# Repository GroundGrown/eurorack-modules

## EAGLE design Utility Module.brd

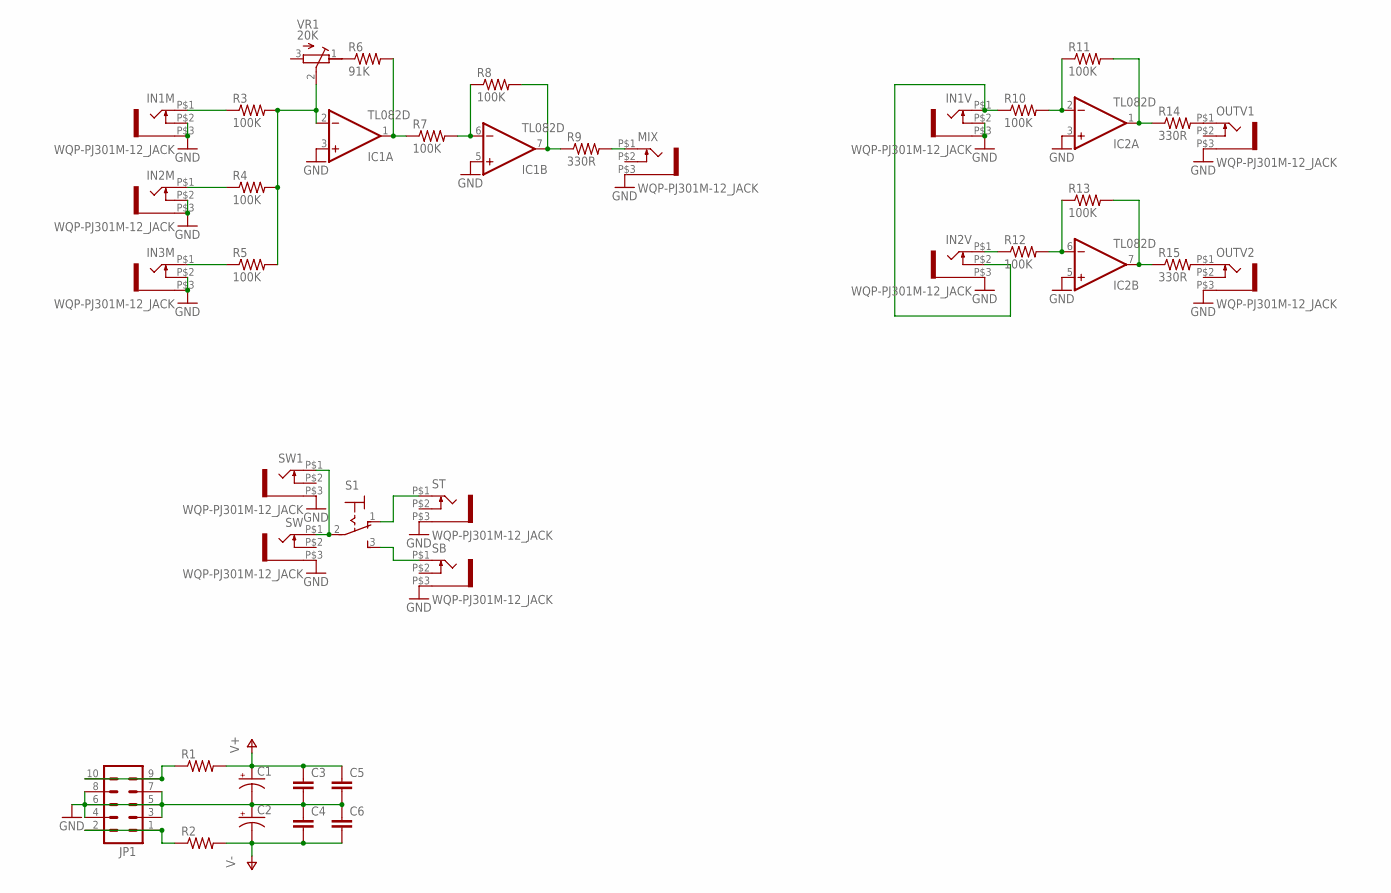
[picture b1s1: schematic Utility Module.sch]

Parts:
C1, C2: CAP_POLC; PANASONIC_C
C3, C4, C5, C6: CAP0805; 0805
IC1, IC2: TL082D; SO08
IN1M, IN1V, IN2M, IN2V, IN3M: WQP-PJ301M-12_JACK
JP1: M05X2PTH; AVR_ICSP
MIX: WQP-PJ301M-12_JACK
OUTV1, OUTV2: WQP-PJ301M-12_JACK
R1, R2: RESISTOR0805-RES; 0805
R3, R4, R5, R7, R8, R10, R11, R12, R13: 100K; 0805
R6: 91K; 0805
R9, R14, R15: 330R; 0805
S1: M9040P
SB: WQP-PJ301M-12_JACK
ST: WQP-PJ301M-12_JACK
SW, SW1: WQP-PJ301M-12_JACK
VR1: 20K; RTRIM3314G

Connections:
GND: C1.-, C2.+, C3.2, C4.1, C5.2, C6.1, IC1.3 (+IN), IC1.5 (+IN), IC2.3 (+IN), IC2.5 (+IN), IN1M.P$2 (3), IN1M.P$3 (1), IN1V.P$2 (3), IN1V.P$3 (1), IN2M.P$2 (3), IN2M.P$3 (1), IN2V.P$3 (1), IN3M.P$2 (3), IN3M.P$3 (1), JP1.3, JP1.4, JP1.5, JP1.6, JP1.7, JP1.8, MIX.P$3 (1), OUTV1.P$3 (1), OUTV2.P$3 (1), SB.P$3 (1), ST.P$3 (1), SW.P$3 (1), SW1.P$3 (1)
unnamed: R6.1, VR1.1 (E)
unnamed: IN1M.P$1 (2), R3.1
unnamed: JP1.9, JP1.10, R1.1
unnamed: JP1.1, JP1.2, R2.1
unnamed: IN2M.P$1 (2), R4.1
unnamed: IN3M.P$1 (2), R5.1
unnamed: IC1.2 (-IN), R3.2, R4.2, R5.2, VR1.2 (S)
unnamed: MIX.P$1 (2), R9.2
unnamed: IC1.1 (OUT), R6.2, R7.1
unnamed: IC1.6 (-IN), R7.2, R8.1
unnamed: IC1.7 (OUT), R8.2, R9.1
unnamed: IN1V.P$1 (2), IN2V.P$2 (3), R10.1
unnamed: S1.2, SW.P$1 (2), SW1.P$1 (2)
unnamed: IN2V.P$1 (2), R12.1
unnamed: IC2.6 (-IN), R12.2, R13.1
unnamed: IC2.2 (-IN), R10.2, R11.1
unnamed: IC2.1 (OUT), R11.2, R14.1
unnamed: IC2.7 (OUT), R13.2, R15.1
unnamed: OUTV1.P$1 (2), R14.2
unnamed: OUTV2.P$1 (2), R15.2
unnamed: S1.1 (O), ST.P$1 (2)
unnamed: S1.3 (S), SB.P$1 (2)
V+: C1.+, C3.1, C5.1, IC1.8 (V+), IC2.8 (V+), R1.2
V-: C2.-, C4.2, C6.2, IC1.4 (V-), IC2.4 (V-), R2.2

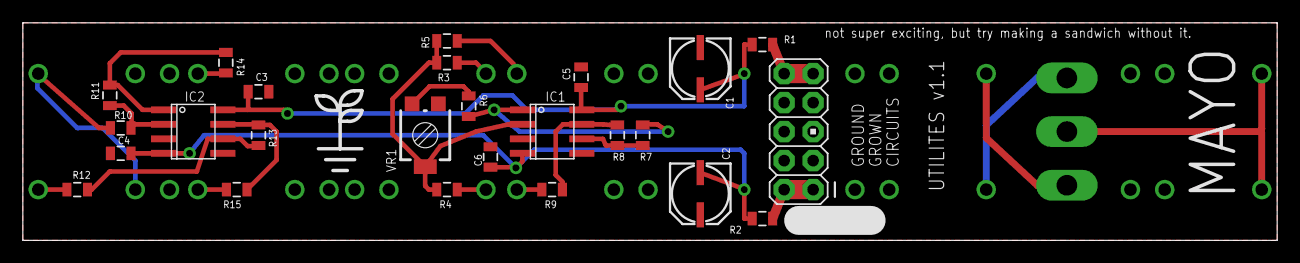
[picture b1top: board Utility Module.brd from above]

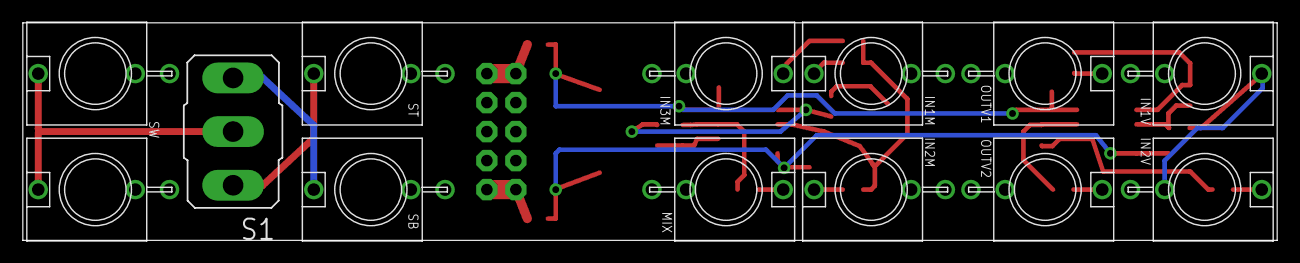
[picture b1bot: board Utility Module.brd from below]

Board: 2 copper layers, 109.9 x 19.1 mm, 39 parts (13 on the bottom side), 25 nets.

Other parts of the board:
U$1: LOGO_SMALL

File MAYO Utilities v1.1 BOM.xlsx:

2 | FERRITE BEAD | R1, R2
3 | 330 ohm | R9, R14, R15
1 | 91K | R6
9 | 100K | R3, R4, R5, R7, R8, R10, R11, R12, R13
4 | .1u | C3, C4, C5, C6
2 | 10u | C1, C2
1 | 20K Trim | VR1
2 | TL082 | IC1, IC2
1 | 2x5 pos male .1" Header | JP1
12 | WQP-PJ301M-12_JACK | IN1M, IN2M, IN3M, MIX, IN1V, IN2V, OUTV1, OUTV2, SW, SW1, ST, SB
1 | ON-OFF-ON toggle M9040P | S1

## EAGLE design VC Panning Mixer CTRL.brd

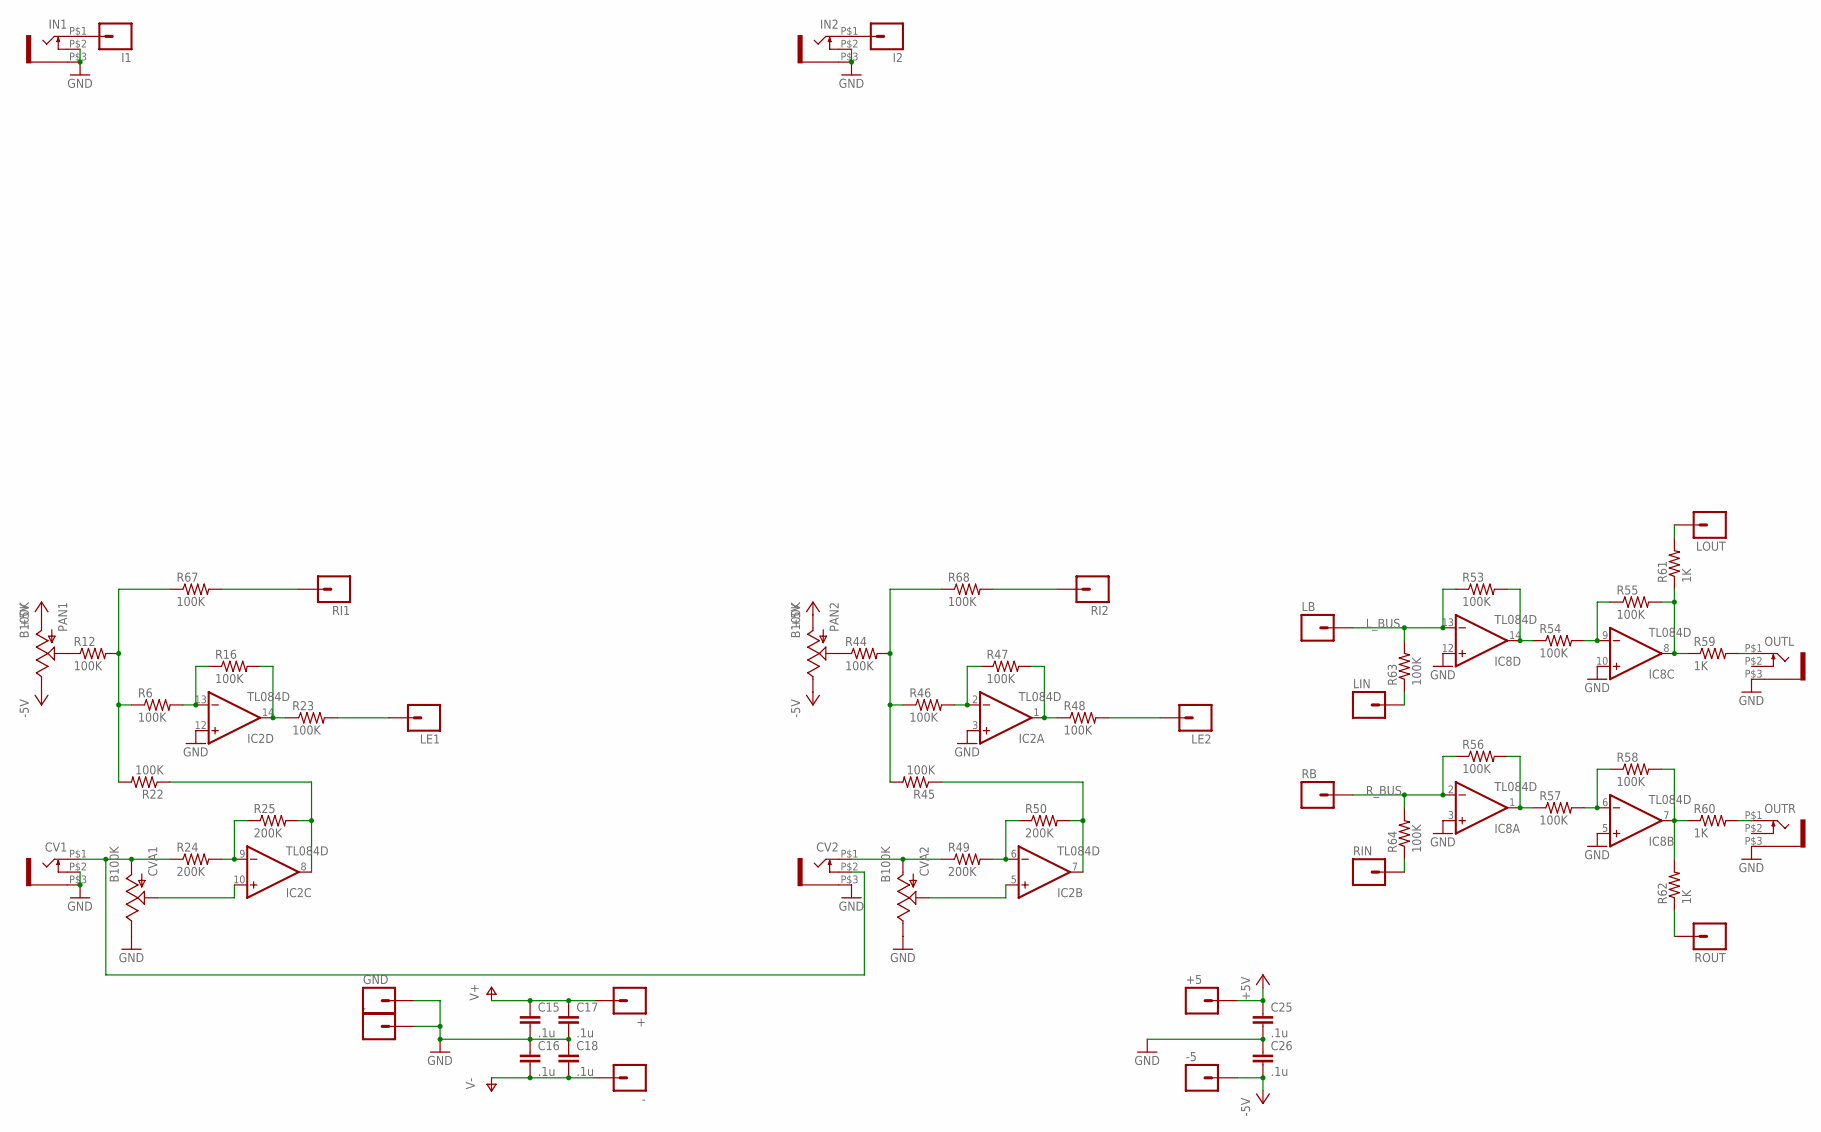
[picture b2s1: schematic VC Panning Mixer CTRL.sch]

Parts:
+, +5: M01PTH; 1X01
-, -5: M01PTH; 1X01
.: M01PTH; 1X01
C15, C16, C17, C18, C25, C26: .1u; 0805
CV1, CV2: WQP-PJ301M-12_JACK
CVA1, CVA2: B100K; ALPS_POT
GND: M01PTH; 1X01
I1, I2: M01PTH; 1X01
IC2, IC8: TL084D; SO14
IN1, IN2: WQP-PJ301M-12_JACK
LB: M01PTH; 1X01
LE1, LE2: M01PTH; 1X01
LIN: M01PTH; 1X01
LOUT: M01PTH; 1X01
OUTL: WQP-PJ301M-12_JACK
OUTR: WQP-PJ301M-12_JACK
PAN1, PAN2: B100K; ALPS_POT
R6, R12, R16, R22, R23, R44, R45, R46, R47, R48, R53, R54, R55, R56, R57, R58, R63, R64, R67, R68: 100K; 0805
R24, R25, R49, R50: 200K; 0805
R59, R60, R61, R62: 1K; 0805
RB: M01PTH; 1X01
RI1, RI2: M01PTH; 1X01
RIN: M01PTH; 1X01
ROUT: M01PTH; 1X01

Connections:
+5V: +5.1, C25.1, PAN1.P$3 (A), PAN2.P$3 (A)
-5V: -5.1, C26.2, PAN1.P$1 (E), PAN2.P$1 (E)
GND: ..1, C15.2, C16.1, C17.2, C18.1, C25.2, C26.1, CV1.P$2 (3), CV1.P$3 (1), CV2.P$3 (1), CVA1.P$1 (E), CVA2.P$1 (E), GND.1, IC2.3 (+IN), IC2.12 (+IN), IC8.3 (+IN), IC8.5 (+IN), IC8.10 (+IN), IC8.12 (+IN), IN1.P$2 (3), IN1.P$3 (1), IN2.P$2 (3), IN2.P$3 (1), OUTL.P$3 (1), OUTR.P$3 (1)
L_BUS: IC8.13 (-IN), LB.1, R53.1, R63.2
unnamed: R68.2, RI2.1
unnamed: R67.2, RI1.1
unnamed: I1.1, IN1.P$1 (2)
unnamed: I2.1, IN2.P$1 (2)
unnamed: R6.1, R12.2, R22.2, R67.1
unnamed: LE1.1, R23.2
unnamed: LE2.1, R48.2
unnamed: R44.2, R45.2, R46.1, R68.1
unnamed: PAN1.P$2 (S), R12.1
unnamed: CV1.P$1 (2), CV2.P$2 (3), CVA1.P$3 (A), R24.1
unnamed: CVA1.P$2 (S), IC2.10 (+IN)
unnamed: IC2.9 (-IN), R24.2, R25.1
unnamed: IC2.8 (OUT), R22.1, R25.2
unnamed: IC2.13 (-IN), R6.2, R16.1
unnamed: IC2.14 (OUT), R16.2, R23.1
unnamed: PAN2.P$2 (S), R44.1
unnamed: CV2.P$1 (2), CVA2.P$3 (A), R49.1
unnamed: CVA2.P$2 (S), IC2.5 (+IN)
unnamed: IC2.6 (-IN), R49.2, R50.1
unnamed: IC2.7 (OUT), R45.1, R50.2
unnamed: IC2.2 (-IN), R46.2, R47.1
unnamed: IC2.1 (OUT), R47.2, R48.1
unnamed: IC8.14 (OUT), R53.2, R54.1
unnamed: IC8.9 (-IN), R54.2, R55.1
unnamed: IC8.8 (OUT), R55.2, R59.1, R61.1
unnamed: IC8.1 (OUT), R56.2, R57.1
unnamed: IC8.6 (-IN), R57.2, R58.1
unnamed: IC8.7 (OUT), R58.2, R60.1, R62.2
unnamed: OUTL.P$1 (2), R59.2
unnamed: OUTR.P$1 (2), R60.2
unnamed: R64.1, RIN.1
unnamed: LIN.1, R63.1
unnamed: LOUT.1, R61.2
unnamed: R62.1, ROUT.1
R_BUS: IC8.2 (-IN), R56.1, R64.2, RB.1
V+: +.1, C15.1, C17.1, IC2.4 (V+), IC8.4 (V+)
V-: -.1, C16.2, C18.2, IC2.11 (V-), IC8.11 (V-)

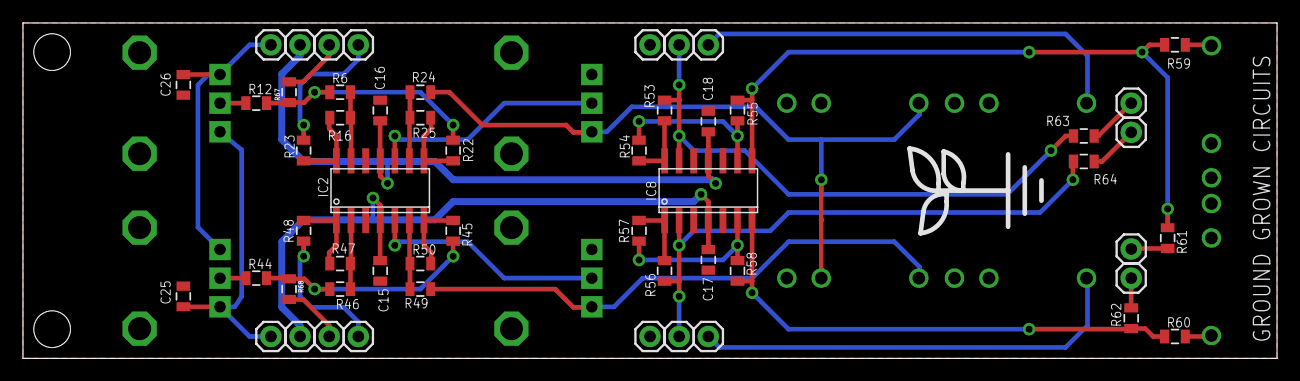
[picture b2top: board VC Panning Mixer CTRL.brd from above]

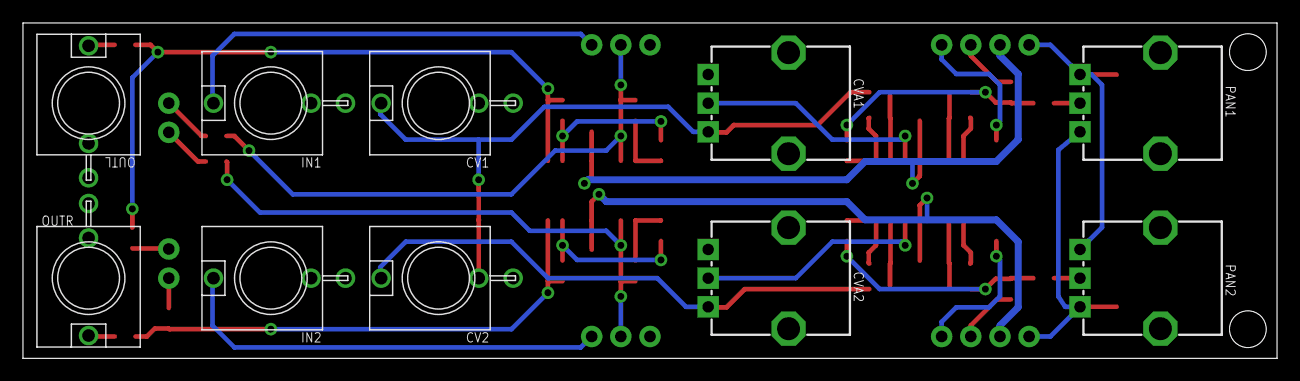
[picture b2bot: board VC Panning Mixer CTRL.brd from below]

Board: 2 copper layers, 109.2 x 29.2 mm, 65 parts (10 on the bottom side), 41 nets.

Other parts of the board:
U$1: LOGO_MED

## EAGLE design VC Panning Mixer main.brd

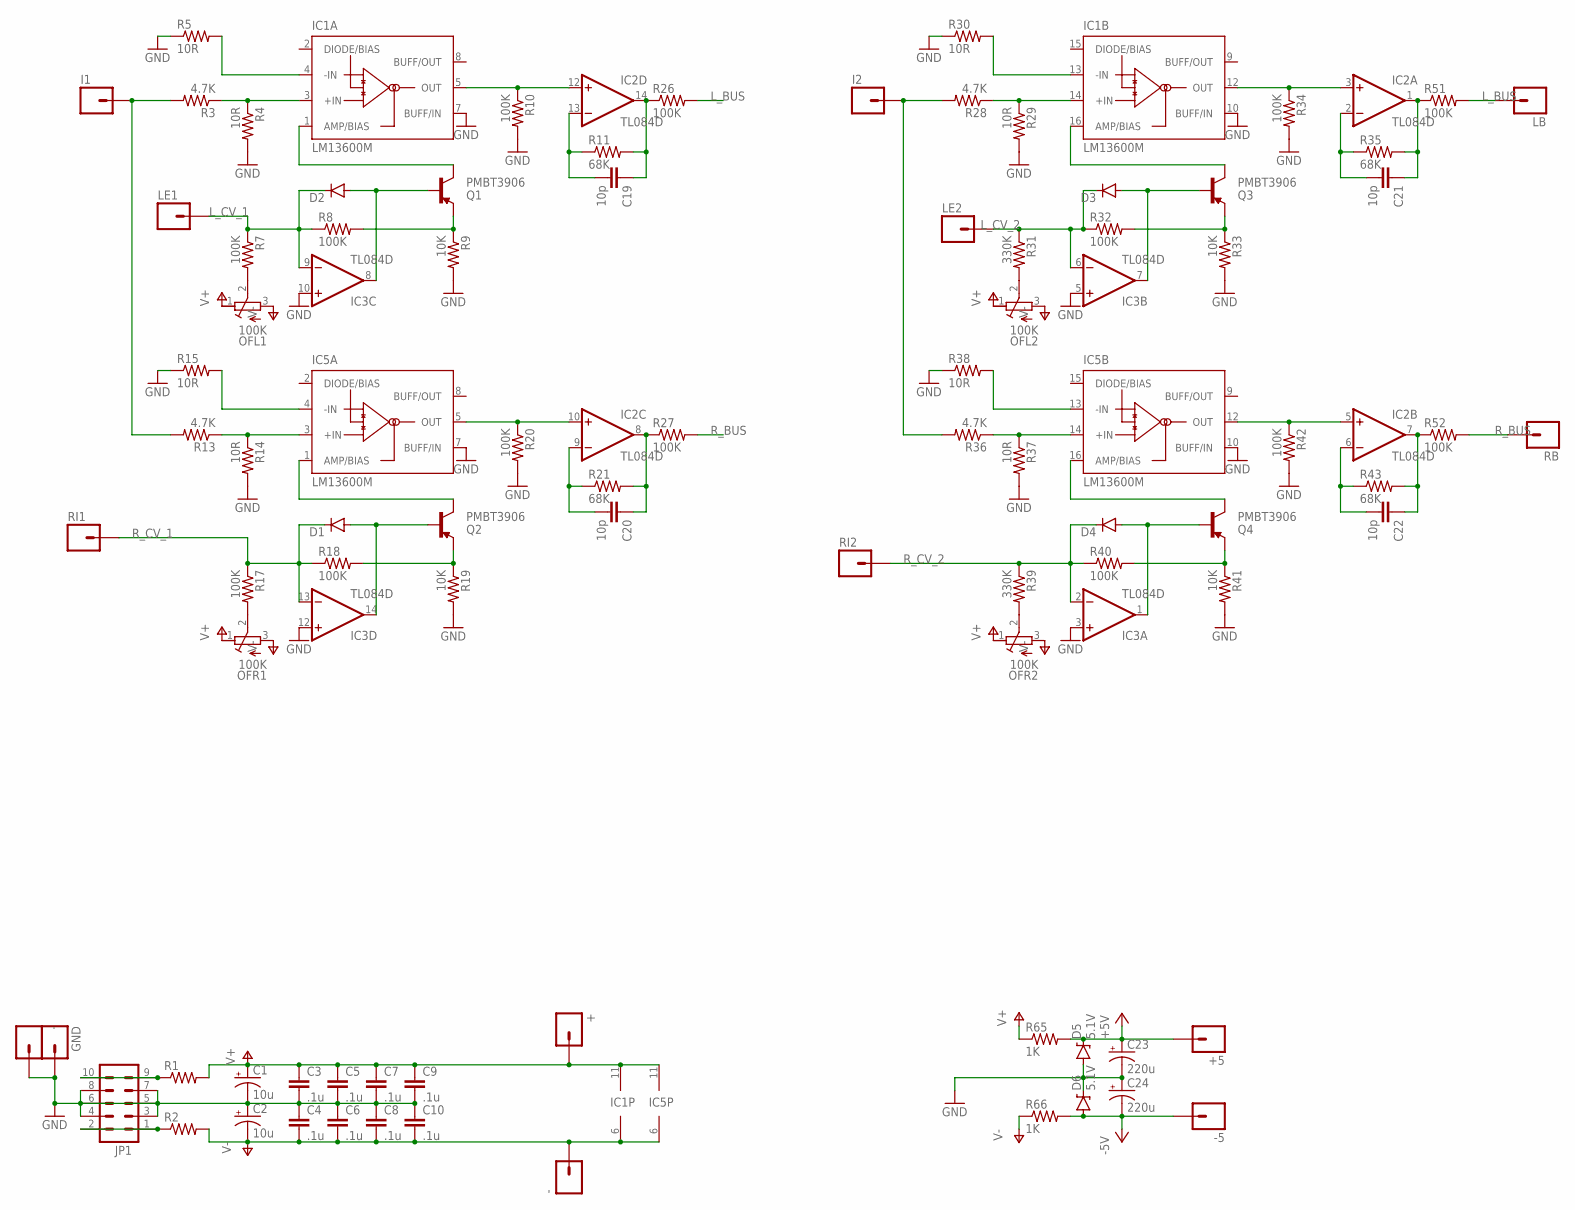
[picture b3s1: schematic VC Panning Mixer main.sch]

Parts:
+, +5: M01PTH; 1X01
-, -5: M01PTH; 1X01
.: M01PTH; 1X01
C1, C2: 10u; CPOL-RADIAL-10UF-25V
C3, C4, C5, C6, C7, C8, C9, C10: .1u; 0805
C19, C20, C21, C22: 10p; 0805
C23, C24: 220u; CPOL-RADIAL-10UF-25V
D1, D2, D3, D4: DIODESOD123; SOD-123
D5, D6: 5.1V; SOD-123
GND: M01PTH; 1X01
I1, I2: M01PTH; 1X01
IC1, IC5: LM13600M; SO16
IC2, IC3: TL084D; SO14
JP1: M05X2PTH; AVR_ICSP
LB: M01PTH; 1X01
LE1, LE2: M01PTH; 1X01
OFL1, OFL2: 100K; RTRIM3314G
OFR1, OFR2: 100K; RTRIM3314G
Q1, Q2, Q3, Q4: PMBT3906; SOT23-3
R1, R2: RESISTOR0805-RES; 0805@1
R3, R13, R28, R36: 4.7K; 0805
R4, R5, R14, R15, R29, R30, R37, R38: 10R; 0805
R7, R8, R10, R17, R18, R20, R26, R27, R32, R34, R40, R42, R51, R52: 100K; 0805
R9, R19, R33, R41: 10K; 0805
R11, R21, R35, R43: 68K; 0805
R31, R39: 330K; 0805
R65, R66: 1K; 0805
RB: M01PTH; 1X01
RI1, RI2: M01PTH; 1X01

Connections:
+5V: +5.1, C23.1 (+), D5.C, R65.2
-5V: -5.1, C24.2 (-), D6.A, R66.2
GND: ..1, C1.2 (-), C2.1 (+), C3.2, C4.1, C5.2, C6.1, C7.2, C8.1, C9.2, C10.1, C23.2 (-), C24.1 (+), D5.A, D6.C, GND.1, IC1.7 (BUFF/IN), IC1.10 (BUFF/IN), IC3.3 (+IN), IC3.5 (+IN), IC3.10 (+IN), IC3.12 (+IN), IC5.7 (BUFF/IN), IC5.10 (BUFF/IN), JP1.3, JP1.4, JP1.5, JP1.6, JP1.7, JP1.8, R4.2, R5.1, R9.2, R10.2, R14.2, R15.1, R19.2, R20.2, R29.2, R30.1, R33.2, R34.2, R37.2, R38.1, R41.2, R42.2
L_BUS: LB.1, R26.2, R51.2
L_CV_1: D2.C, IC3.9 (-IN), LE1.1, R7.1, R8.1
L_CV_2: D3.C, IC3.6 (-IN), LE2.1, R31.1, R32.1
unnamed: JP1.9, JP1.10, R1.1
unnamed: JP1.1, JP1.2, R2.1
unnamed: I1.1, R3.2, R13.2
unnamed: IC5.3 (+IN), R13.1, R14.1
unnamed: IC5.4 (-IN), R15.2
unnamed: OFR1.2 (S), R17.2
unnamed: Q2.2 (E), R18.2, R19.1
unnamed: D1.A, IC3.14 (OUT), Q2.1 (B)
unnamed: IC5.1 (AMP/BIAS), Q2.3 (C)
unnamed: IC1.3 (+IN), R3.1, R4.1
unnamed: IC2.10 (+IN), IC5.5 (OUT), R20.1
unnamed: IC1.4 (-IN), R5.2
unnamed: OFL1.2 (S), R7.2
unnamed: Q1.2 (E), R8.2, R9.1
unnamed: D2.A, IC3.8 (OUT), Q1.1 (B)
unnamed: C20.2, IC2.9 (-IN), R21.1
unnamed: IC1.1 (AMP/BIAS), Q1.3 (C)
unnamed: IC1.5 (OUT), IC2.12 (+IN), R10.1
unnamed: C19.2, IC2.13 (-IN), R11.1
unnamed: C19.1, IC2.14 (OUT), R11.2, R26.1
unnamed: C20.1, IC2.8 (OUT), R21.2, R27.1
unnamed: IC1.14 (+IN), R28.1, R29.1
unnamed: IC1.13 (-IN), R30.2
unnamed: OFL2.2 (S), R31.2
unnamed: Q3.2 (E), R32.2, R33.1
unnamed: D3.A, IC3.7 (OUT), Q3.1 (B)
unnamed: IC1.16 (AMP/BIAS), Q3.3 (C)
unnamed: IC1.12 (OUT), IC2.3 (+IN), R34.1
unnamed: C21.2, IC2.2 (-IN), R35.1
unnamed: C21.1, IC2.1 (OUT), R35.2, R51.1
unnamed: I2.1, R28.2, R36.2
unnamed: IC5.14 (+IN), R36.1, R37.1
unnamed: IC5.13 (-IN), R38.2
unnamed: OFR2.2 (S), R39.2
unnamed: Q4.2 (E), R40.2, R41.1
unnamed: D4.A, IC3.1 (OUT), Q4.1 (B)
unnamed: IC5.16 (AMP/BIAS), Q4.3 (C)
unnamed: IC2.5 (+IN), IC5.12 (OUT), R42.1
unnamed: C22.2, IC2.6 (-IN), R43.1
unnamed: C22.1, IC2.7 (OUT), R43.2, R52.1
R_BUS: R27.2, R52.2, RB.1
R_CV_1: D1.C, IC3.13 (-IN), R17.1, R18.1, RI1.1
R_CV_2: D4.C, IC3.2 (-IN), R39.1, R40.1, RI2.1
V+: +.1, C1.1 (+), C3.1, C5.1, C7.1, C9.1, IC1.11 (V+), IC2.4 (V+), IC3.4 (V+), IC5.11 (V+), OFL1.1 (E), OFL2.1 (E), OFR1.1 (E), OFR2.1 (E), R1.2, R65.1
V-: -.1, C2.2 (-), C4.2, C6.2, C8.2, C10.2, IC1.6 (V-), IC2.11 (V-), IC3.11 (V-), IC5.6 (V-), OFL1.3 (A), OFL2.3 (A), OFR1.3 (A), OFR2.3 (A), R2.2, R66.1

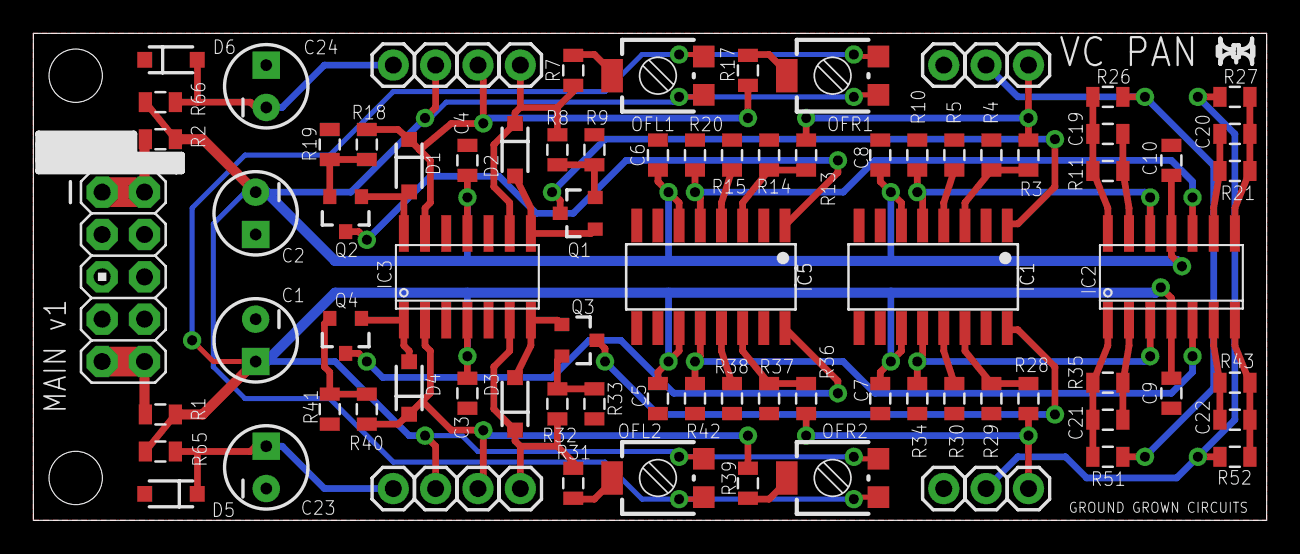
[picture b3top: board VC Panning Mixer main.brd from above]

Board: 2 copper layers, 74.0 x 29.2 mm, 90 parts (1 on the bottom side), 51 nets.

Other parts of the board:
U$1: LOGO_LARGE

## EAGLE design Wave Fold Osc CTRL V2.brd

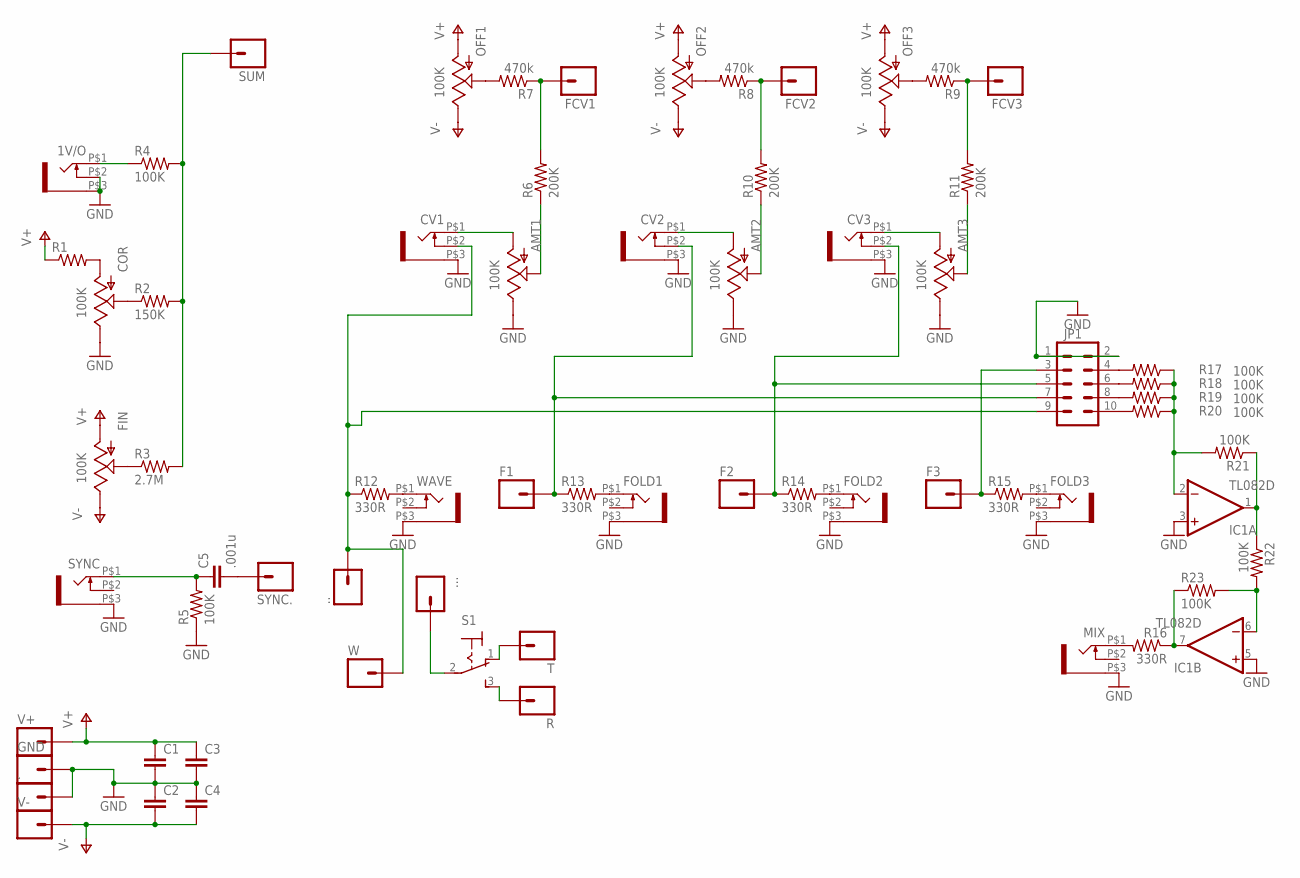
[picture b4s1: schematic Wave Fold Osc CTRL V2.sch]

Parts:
1V/O: WQP-PJ301M-12_JACK
., .., ...: M01PTH; 1X01
AMT1, AMT2, AMT3: 100K; ALPS_POT
C1, C2, C3, C4: CAP0805; 0805
C5: .001u; 0805
COR: 100K; ALPS_POT
CV1, CV2, CV3: WQP-PJ301M-12_JACK
F1, F2, F3: M01PTH; 1X01
FCV1, FCV2, FCV3: M01PTH; 1X01
FIN: 100K; ALPS_POT
FOLD1, FOLD2, FOLD3: WQP-PJ301M-12_JACK
GND: M01PTH; 1X01
IC1: TL082D; SO08
JP1: M05X2NO_SILK; 2X5_NOSILK
MIX: WQP-PJ301M-12_JACK
OFF1, OFF2, OFF3: 100K; ALPS_POT
R: M01PTH; 1X01
R1: RESISTOR0805-RES; 0805
R2: 150K; 0805
R3: 2.7M; 0805
R4, R5, R17, R18, R19, R20, R21, R22, R23: 100K; 0805
R6, R10, R11: 200K; 0805
R7, R8, R9: 470k; 0805
R12, R13, R14, R15, R16: 330R; 0805
S1: M9040P
SUM: M01PTH; 1X01
SYNC: WQP-PJ301M-12_JACK
SYNC.: M01PTH; 1X01
T: M01PTH; 1X01
V+: M01PTH; 1X01
V-: M01PTH; 1X01
W: M01PTH; 1X01
WAVE: WQP-PJ301M-12_JACK

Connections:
GND: 1V/O.P$2 (3), 1V/O.P$3 (1), ..1, AMT1.P$1 (E), AMT2.P$1 (E), AMT3.P$1 (E), C1.2, C2.1, C3.2, C4.1, COR.P$1 (E), CV1.P$3 (1), CV2.P$3 (1), CV3.P$3 (1), FOLD1.P$3 (1), FOLD2.P$3 (1), FOLD3.P$3 (1), GND.1, IC1.3 (+IN), IC1.5 (+IN), JP1.1, JP1.2, MIX.P$3 (1), R5.1, SYNC.P$3 (1), WAVE.P$3 (1)
unnamed: COR.P$3 (A), R1.2
unnamed: COR.P$2 (S), R2.1
unnamed: FIN.P$2 (S), R3.1
unnamed: 1V/O.P$1 (2), R4.1
unnamed: ...1, CV1.P$2 (3), JP1.9, R12.1, W.1
unnamed: OFF1.P$2 (S), R7.2
unnamed: R2.2, R3.2, R4.2, SUM.1
unnamed: C5.2, SYNC..1
unnamed: AMT1.P$3 (A), CV1.P$1 (2)
unnamed: AMT1.P$2 (S), R6.1
unnamed: FCV1.1, R6.2, R7.1
unnamed: OFF2.P$2 (S), R8.2
unnamed: OFF3.P$2 (S), R9.2
unnamed: AMT2.P$3 (A), CV2.P$1 (2)
unnamed: AMT2.P$2 (S), R10.1
unnamed: FCV2.1, R8.1, R10.2
unnamed: AMT3.P$3 (A), CV3.P$1 (2)
unnamed: AMT3.P$2 (S), R11.1
unnamed: FCV3.1, R9.1, R11.2
unnamed: R12.2, WAVE.P$1 (2)
unnamed: JP1.4, R17.2
unnamed: FOLD1.P$1 (2), R13.2
unnamed: FOLD2.P$1 (2), R14.2
unnamed: FOLD3.P$1 (2), R15.2
unnamed: MIX.P$1 (2), R16.2
unnamed: JP1.6, R18.2
unnamed: JP1.8, R19.2
unnamed: JP1.10, R20.2
unnamed: IC1.1 (OUT), R21.1, R22.1
unnamed: C5.1, R5.2, SYNC.P$1 (2)
unnamed: CV2.P$2 (3), F1.1, JP1.7, R13.1
unnamed: CV3.P$2 (3), F2.1, JP1.5, R14.1
unnamed: F3.1, JP1.3, R15.1
unnamed: IC1.2 (-IN), R17.1, R18.1, R19.1, R20.1, R21.2
unnamed: IC1.6 (-IN), R22.2, R23.2
unnamed: IC1.7 (OUT), R16.1, R23.1
unnamed: R.1, S1.3 (S)
unnamed: S1.1 (O), T.1
unnamed: ....1, S1.2
V+: C1.1, C3.1, FIN.P$3 (A), IC1.8 (V+), OFF1.P$3 (A), OFF2.P$3 (A), OFF3.P$3 (A), R1.1, V+.1
V-: C2.2, C4.2, FIN.P$1 (E), IC1.4 (V-), OFF1.P$1 (E), OFF2.P$1 (E), OFF3.P$1 (E), V-.1

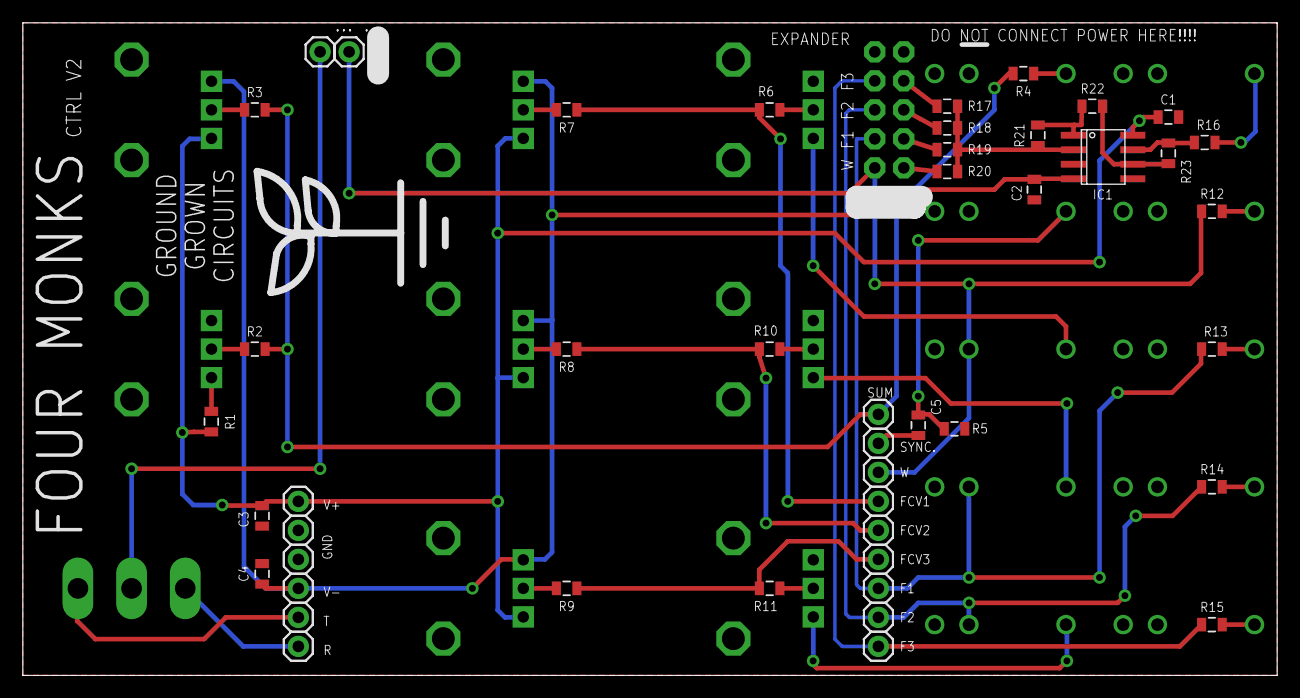
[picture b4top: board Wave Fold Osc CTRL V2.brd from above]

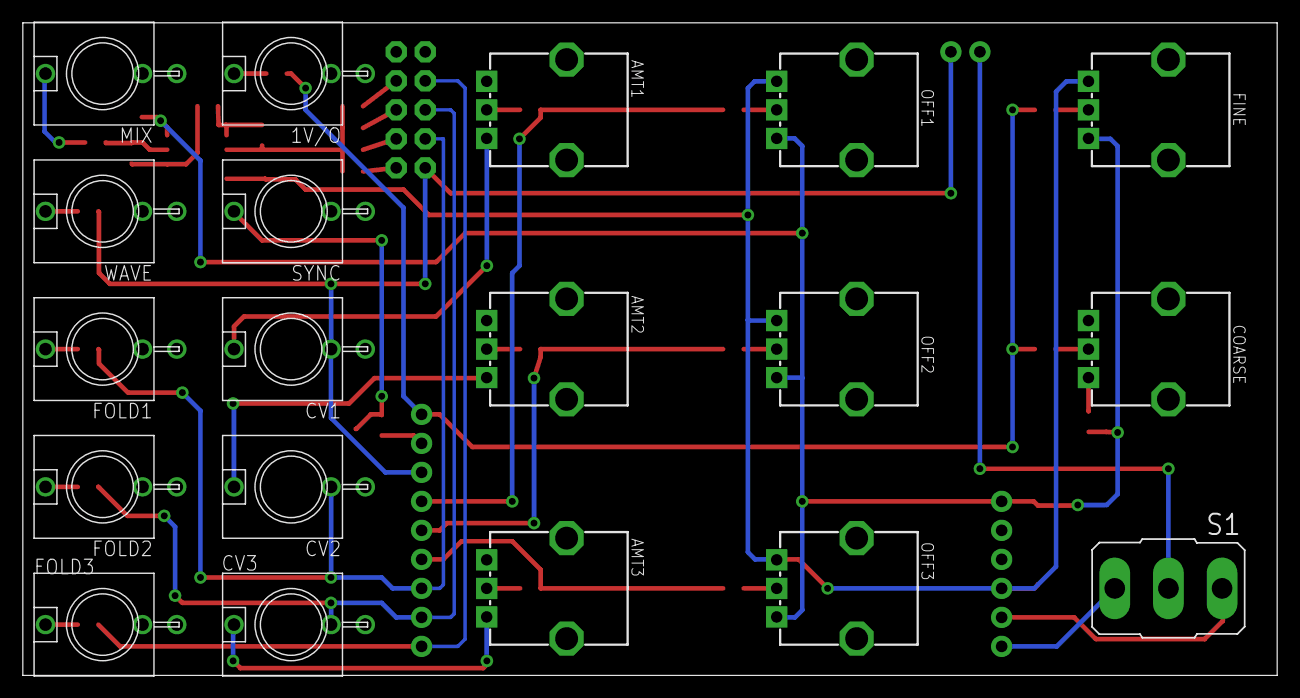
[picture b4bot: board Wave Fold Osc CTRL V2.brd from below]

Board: 2 copper layers, 109.9 x 57.1 mm, 67 parts (19 on the bottom side), 42 nets.

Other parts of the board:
U$2: LOGO_LARGE

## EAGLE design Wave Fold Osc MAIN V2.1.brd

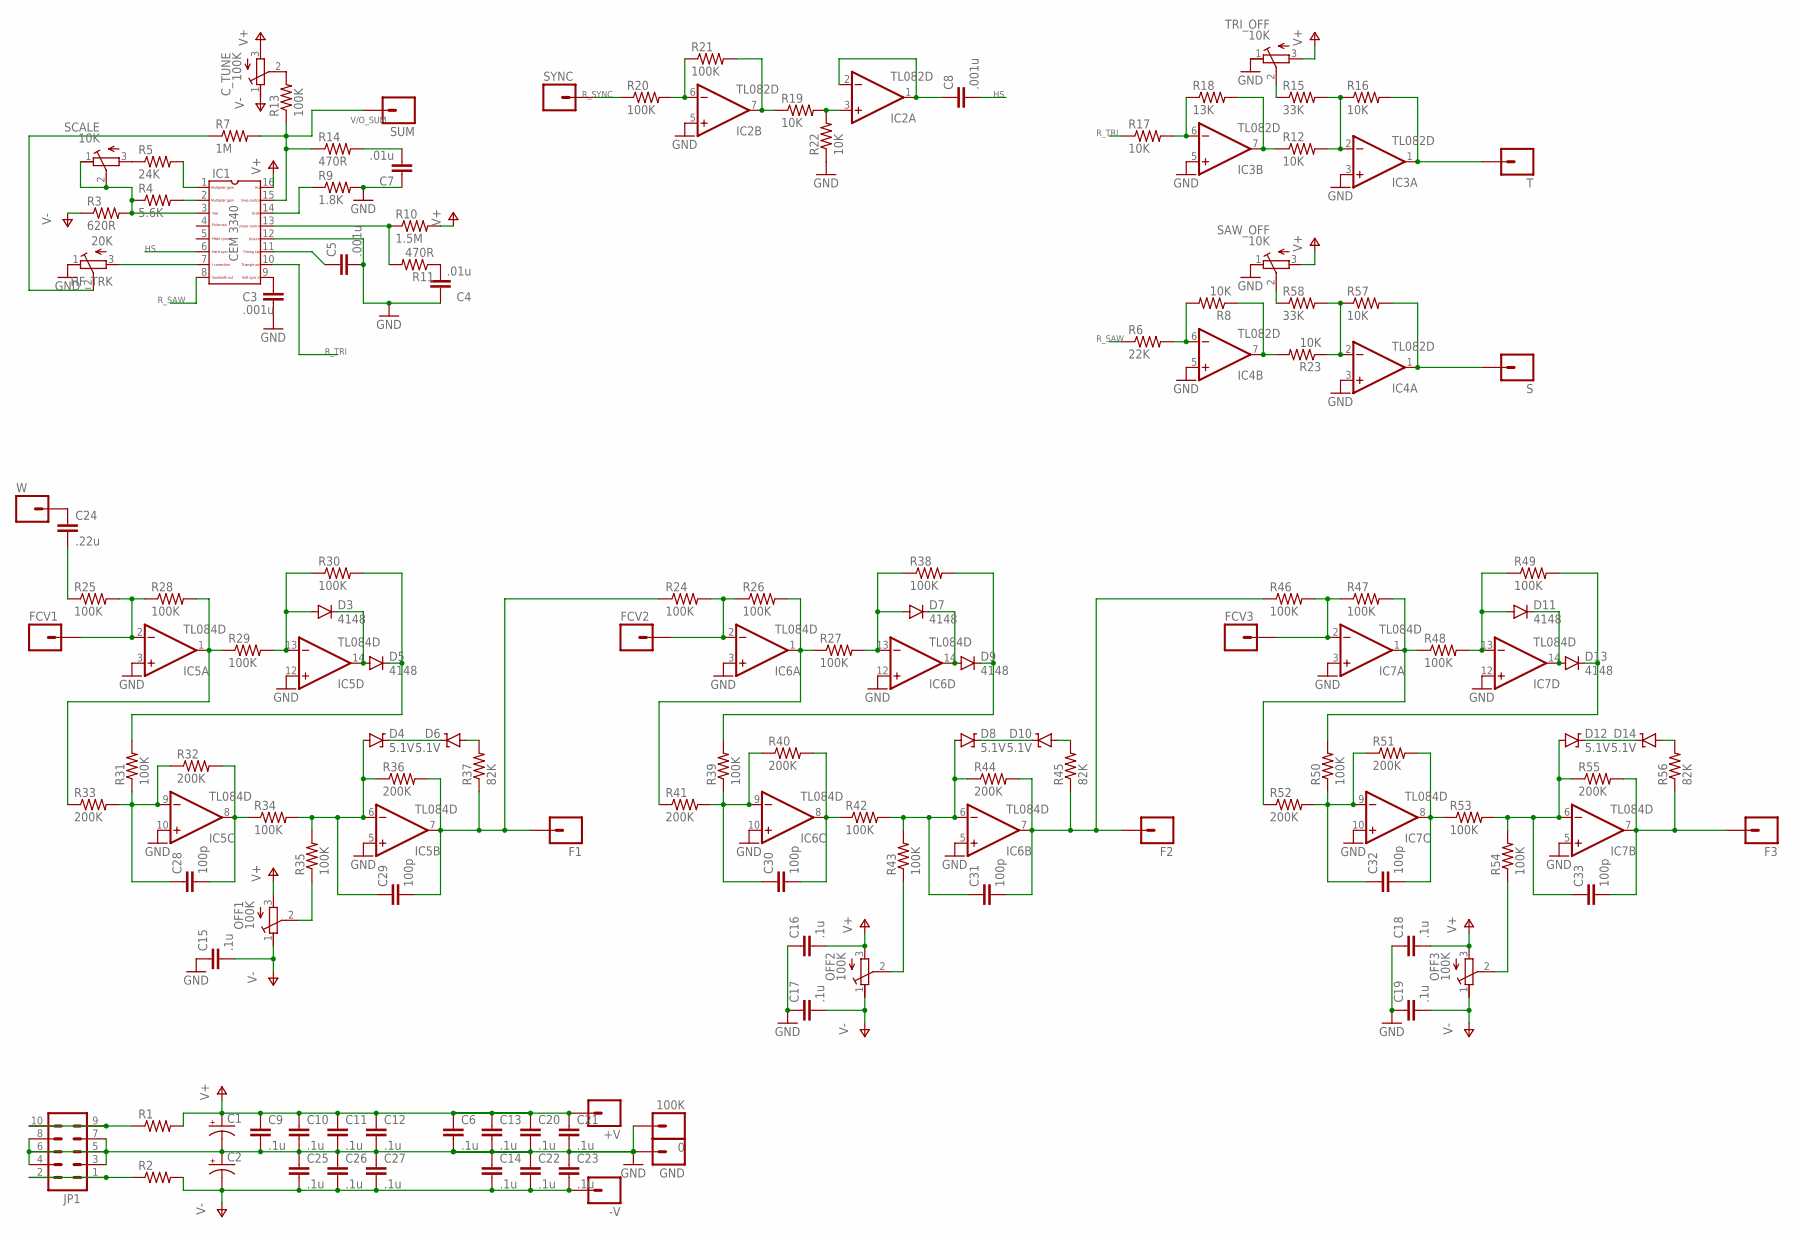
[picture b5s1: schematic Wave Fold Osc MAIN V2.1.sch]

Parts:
0: 100K; 1X01
+V: M01PTH; 1X01
-V: M01PTH; 1X01
C1, C2: CAP_POLC; PANASONIC_C
C3, C8: .001u; 0805
C4, C7: .01u; 0805
C5: .001u; C5B2.5
C6, C9, C10, C11, C12, C13, C14, C20, C21, C22, C23, C25, C26, C27: .1u; 0805@1
C15, C16, C17, C18, C19: .1u; 0805
C24: .22u; 0805@1
C28, C29, C30, C31, C32, C33: 100p; 0805@1
C_TUNE: 100K; RTRIM3314G
D3, D5, D7, D9, D11, D13: 4148; SOD-123
D4, D6, D8, D10, D12, D14: 5.1V; SOD-123
F1, F2, F3: M01PTH; 1X01
FCV1, FCV2, FCV3: M01PTH; 1X01
GND: M01PTH; 1X01
HF_TRK: 20K; RTRIM3314G
IC1: CEM3340_SMD; SO16
IC2, IC3, IC4: TL082D; SO08
IC5, IC6, IC7: TL084D; SO14
JP1: M05X2PTH; AVR_ICSP
OFF1, OFF2, OFF3: 100K; RTRIM3314G
R1, R2: RESISTOR0805-RES; 0805
R3: 620R; 0805
R4: 5.6K; 0805
R5: 24K; 0805
R6: 22K; 0805
R7: 1M; 0805
R8, R12, R16, R17, R19, R22, R23, R57: 10K; 0805
R9: 1.8K; 0805
R10: 1.5M; 0805
R11, R14: 470R; 0805
R13, R20, R21, R24, R25, R26, R27, R28, R29, R30, R31, R34, R35, R38, R39, R42, R43, R46, R47, R48, R49, R50, R53, R54: 100K; 0805
R15, R58: 33K; 0805
R18: 13K; 0805
R32, R33, R36, R40, R41, R44, R51, R52, R55: 200K; 0805
R37, R45, R56: 82K; 0805
S: M01PTH; 1X01
SAW_OFF: 10K; RTRIM3314G
SCALE: 10K; RTRIM3314G
SUM: M01PTH; 1X01
SYNC: M01PTH; 1X01
T: M01PTH; 1X01
TRI_OFF: 10K; RTRIM3314G
W: M01PTH; 1X01

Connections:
GND: 0.1, C1.-, C2.+, C3.2, C4.1, C5.2, C6.2, C7.1, C9.2, C10.2, C11.2, C12.2, C13.2, C14.1, C15.1, C16.1, C17.1, C18.1, C19.1, C20.2, C21.2, C22.1, C23.1, C25.1, C26.1, C27.1, GND.1, HF_TRK.1 (E), IC1.12, IC2.5 (+IN), IC3.3 (+IN), IC3.5 (+IN), IC4.3 (+IN), IC4.5 (+IN), IC5.3 (+IN), IC5.5 (+IN), IC5.10 (+IN), IC5.12 (+IN), IC6.3 (+IN), IC6.5 (+IN), IC6.10 (+IN), IC6.12 (+IN), IC7.3 (+IN), IC7.5 (+IN), IC7.10 (+IN), IC7.12 (+IN), JP1.3, JP1.4, JP1.5, JP1.6, JP1.7, JP1.8, R9.2, R22.1, SAW_OFF.1 (E), TRI_OFF.1 (E)
HS: C8.2, IC1.6
LFO_SW: C5.1, IC1.11
unnamed: IC1.3, R3.2, R4.1, SCALE.1 (E), SCALE.2 (S)
unnamed: JP1.9, JP1.10, R1.1
unnamed: JP1.1, JP1.2, R2.1
unnamed: IC1.2, R4.2
unnamed: IC1.1, R5.2
unnamed: R5.1, SCALE.3 (A)
unnamed: HF_TRK.3 (A), IC1.7
unnamed: HF_TRK.2 (S), R7.1
unnamed: C_TUNE.2 (S), R13.2
unnamed: IC1.14, R9.1
unnamed: IC1.13, R10.1, R11.2
unnamed: C3.1, IC1.9
unnamed: IC3.6 (-IN), R17.2, R18.1
unnamed: C7.2, R14.2
unnamed: IC4.6 (-IN), R6.2, R8.2
unnamed: IC4.7 (OUT), R8.1, R23.2
unnamed: C24.1, W.1
unnamed: C4.2, R11.1
unnamed: IC3.7 (OUT), R12.1, R18.2
unnamed: IC3.2 (-IN), R12.2, R15.2, R16.1
unnamed: IC3.1 (OUT), R16.2, T.1
unnamed: R15.1, TRI_OFF.2 (S)
unnamed: IC4.2 (-IN), R23.1, R57.1, R58.2
unnamed: IC2.3 (+IN), R19.2, R22.2
unnamed: IC2.6 (-IN), R20.2, R21.1
unnamed: IC2.7 (OUT), R19.1, R21.2
unnamed: C8.1, IC2.1 (OUT), IC2.2 (-IN)
unnamed: IC4.1 (OUT), R57.2, S.1
unnamed: IC6.1 (OUT), R26.2, R27.1, R41.1
unnamed: FCV2.1, IC6.2 (-IN), R24.2, R26.1
unnamed: IC5.1 (OUT), R28.2, R29.1, R33.1
unnamed: D3.C, D5.A, IC5.14 (OUT)
unnamed: D3.A, IC5.13 (-IN), R29.2, R30.1
unnamed: D5.C, R30.2, R31.2
unnamed: C28.1, IC5.9 (-IN), R31.1, R32.1, R33.2
unnamed: C28.2, IC5.8 (OUT), R32.2, R34.1
unnamed: C29.1, D4.A, IC5.6 (-IN), R34.2, R35.2, R36.1
unnamed: OFF1.2 (S), R35.1
unnamed: D4.C, D6.C
unnamed: D6.A, R37.2
unnamed: C29.2, F1.1, IC5.7 (OUT), R24.1, R36.2, R37.1
unnamed: D7.C, D9.A, IC6.14 (OUT)
unnamed: D7.A, IC6.13 (-IN), R27.2, R38.1
unnamed: D9.C, R38.2, R39.2
unnamed: C30.1, IC6.9 (-IN), R39.1, R40.1, R41.2
unnamed: C30.2, IC6.8 (OUT), R40.2, R42.1
unnamed: C31.1, D8.A, IC6.6 (-IN), R42.2, R43.2, R44.1
unnamed: OFF2.2 (S), R43.1
unnamed: D8.C, D10.C
unnamed: D10.A, R45.2
unnamed: C31.2, F2.1, IC6.7 (OUT), R44.2, R45.1, R46.1
unnamed: IC7.1 (OUT), R47.2, R48.1, R52.1
unnamed: D11.C, D13.A, IC7.14 (OUT)
unnamed: D11.A, IC7.13 (-IN), R48.2, R49.1
unnamed: D13.C, R49.2, R50.2
unnamed: C32.1, IC7.9 (-IN), R50.1, R51.1, R52.2
unnamed: C32.2, IC7.8 (OUT), R51.2, R53.1
unnamed: C33.1, D12.A, IC7.6 (-IN), R53.2, R54.2, R55.1
unnamed: OFF3.2 (S), R54.1
unnamed: D12.C, D14.C
unnamed: D14.A, R56.2
unnamed: C33.2, F3.1, IC7.7 (OUT), R55.2, R56.1
unnamed: C24.2, R25.1
unnamed: FCV3.1, IC7.2 (-IN), R46.2, R47.1
unnamed: FCV1.1, IC5.2 (-IN), R25.2, R28.1
unnamed: R58.1, SAW_OFF.2 (S)
R_SAW: IC1.8, R6.1
R_SYNC: R20.1, SYNC.1
R_TRI: IC1.10, R17.1
V+: +V.1, C1.+, C6.1, C9.1, C10.1, C11.1, C12.1, C13.1, C16.2, C18.2, C20.1, C21.1, C_TUNE.3 (A), IC1.16, IC2.8 (V+), IC3.8 (V+), IC4.8 (V+), IC5.4 (V+), IC6.4 (V+), IC7.4 (V+), OFF1.3 (A), OFF2.3 (A), OFF3.3 (A), R1.2, R10.2, SAW_OFF.3 (A), TRI_OFF.3 (A)
V-: -V.1, C2.-, C14.2, C15.2, C17.2, C19.2, C22.2, C23.2, C25.2, C26.2, C27.2, C_TUNE.1 (E), IC2.4 (V-), IC3.4 (V-), IC4.4 (V-), IC5.11 (V-), IC6.11 (V-), IC7.11 (V-), OFF1.1 (E), OFF2.1 (E), OFF3.1 (E), R2.2, R3.1
V/O_SUM: IC1.15, R7.2, R13.1, R14.1, SUM.1

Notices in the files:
parts and their libraries:
SparkFun-Capacitors: Licensing: Creative Commons ShareAlike 4.0 International - https://creativecommons.org/licenses/by-sa/4.0
